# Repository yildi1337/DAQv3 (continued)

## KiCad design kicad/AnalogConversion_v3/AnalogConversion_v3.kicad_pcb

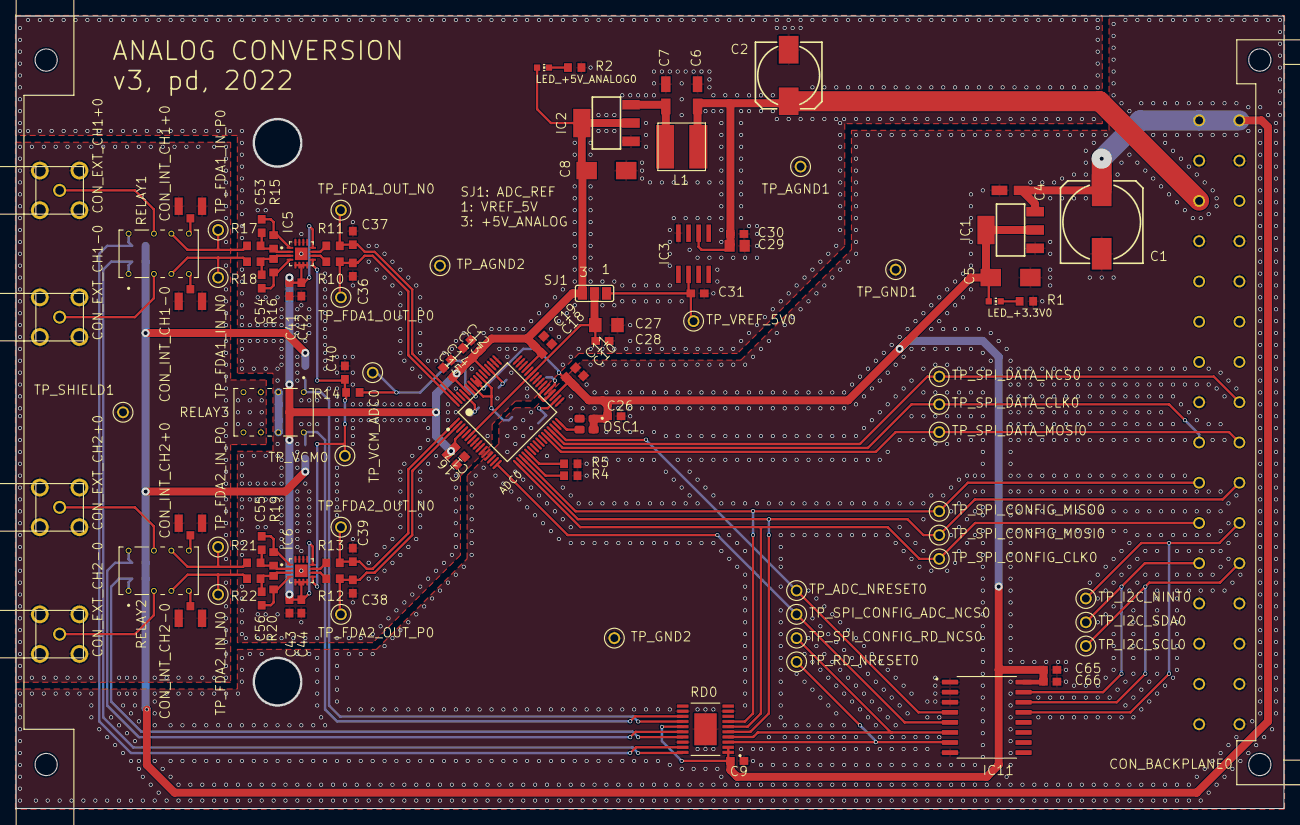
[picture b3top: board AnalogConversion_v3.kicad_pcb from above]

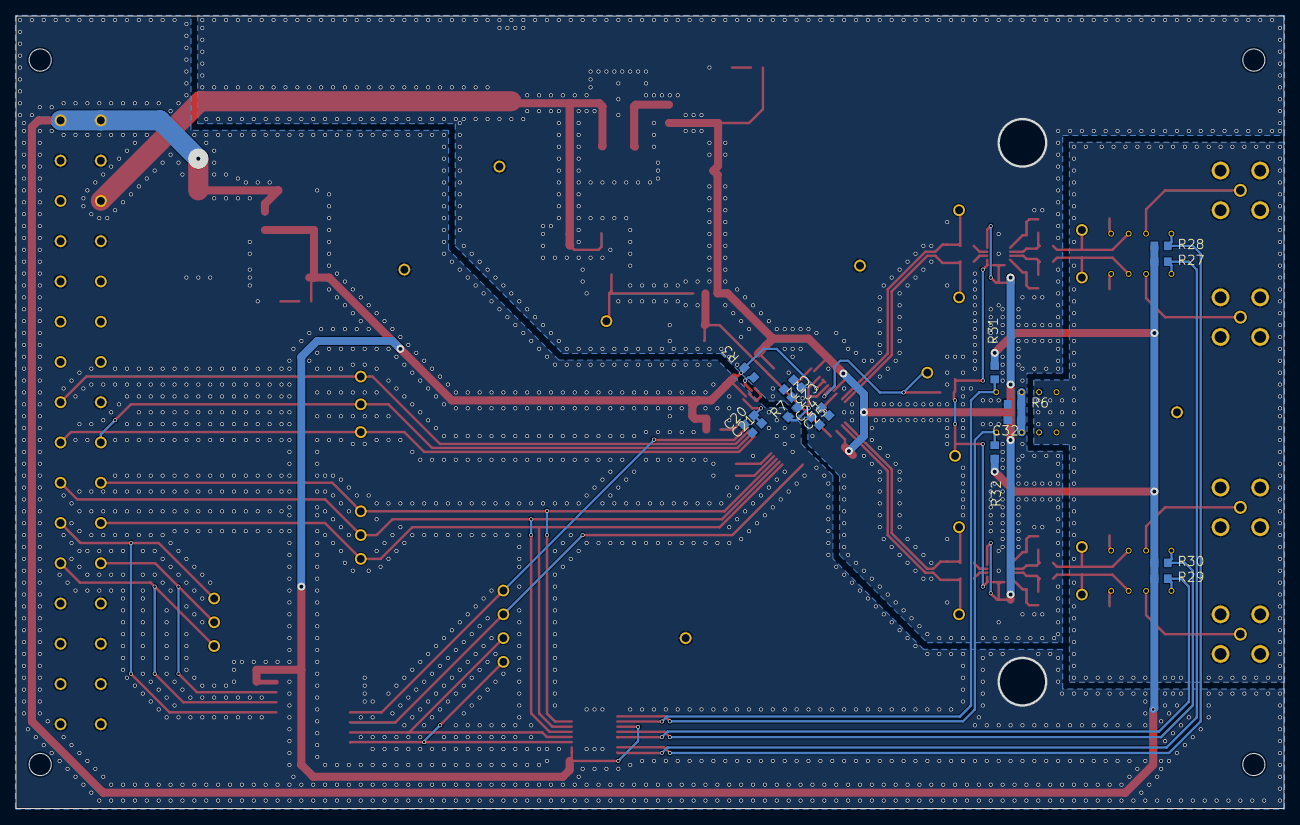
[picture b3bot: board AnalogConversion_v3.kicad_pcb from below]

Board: 2 copper layers, 160.0 x 100.0 mm, 127 parts (16 on the bottom side), 70 nets.

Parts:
ADC0: AD7768-4BSTZ; AD7768-4BSTZ_23633307
C1: 1000u/16V; 153CLV-1010_18640681
C2: 100u/25V; 153CLV-0810_18640681
C4, C6, C7: 10u; CT3216_23469469
C5, C8: 22u; CT6032_23469469
C9, C10, C12, C14, C16, C18, C20, C22, C24, C26, C28, C30, C31, C40, C42, C44, C66: 100n; C0603_23469469
C11, C13, C15, C17, C19, C23, C25, C41, C43, C65: 1u; C0603_23469469
C21: 10u; C0603_23469469
C27: 22u; C1206_23469469
C29: 10u/16V; C0805_23469469
C32: 10n; C0603_23469469
C36, C37, C38, C39: 82p; C0603_23469469
C53, C54, C55, C56: 220p; C0603_23469469
CON_BACKPLANE0: 09031326921; 09031326921_33573412
CON_EXT_CH1+0, CON_EXT_CH1-0, CON_EXT_CH2+0, CON_EXT_CH2-0: DELOCK_65848; DELOCK_65848_34726205
CON_INT_CH1+0, CON_INT_CH1-0, CON_INT_CH2+0, CON_INT_CH2-0: 2337019-1; 2337019-1_28281051
IC1: LM1117IMP-3.3; SOT223_23469477
IC2: LM1117MP-5.0; SOT223_23469477
IC3: ADR445ARZ; ADR445ARZ_35478497
IC5, IC6: ADA4945-1ACPZ-R7; ADA4945-1ACPZ-R7_22669072
IC11: TCA9534ADWR; TCA9534ADWR_34728514
L1: 100u; VLS6045AF-101M_31421361
LED_+3.3V0, LED_+5V_ANALOG0: CHIP-LED0603_259
OSC1: SG-210STF 32.7680ML3; SG-210STF-32.7680ML3_23634516
PCB_BRACKET0: 60807-011; 60807-011_33573280
R1: 750; R0603_23469469
R2: 1.8k; R0603_23469469
R3: 10k; R0603_23469469
R4, R5: 1k; R0603_23469469
R6: 1M; R0603_23469469
R7: 0; R0603_23469469
R10, R11, R12, R13: 82; R0603_23469469
R14: 47; R0603_23469469
R15, R16, R17, R18, R19, R20, R21, R22: 470; R0603_23469469
R27, R28, R29, R30, R31, R32: 100; R0603_23469469
RD0: MAX4820EUP+; MAX4820EUP+_31436371
RELAY1, RELAY2, RELAY3: 5-1462037-8; 5-1462037-8_31429267
SJ1: SJ_2_23508320
TP_ADC_NRESET0: RSPRO-1MM-TERMINAL-POST-2622034_23908750
TP_AGND1, TP_AGND2: RSPRO-1MM-TERMINAL-POST-2622034_23908750
TP_FDA1_IN_N0, TP_FDA1_IN_P0, TP_FDA1_OUT_N0, TP_FDA1_OUT_P0, TP_FDA2_IN_N0, TP_FDA2_IN_P0, TP_FDA2_OUT_N0, TP_FDA2_OUT_P0: RSPRO-1MM-TERMINAL-POST-2622034_23908750
TP_GND1, TP_GND2: RSPRO-1MM-TERMINAL-POST-2622034_23908750
TP_I2C_NINT0, TP_I2C_SCL0, TP_I2C_SDA0: RSPRO-1MM-TERMINAL-POST-2622034_23908750
TP_RD_NRESET0: RSPRO-1MM-TERMINAL-POST-2622034_23908750
TP_SHIELD1: RSPRO-1MM-TERMINAL-POST-2622034_23908750
TP_SPI_CONFIG_ADC_NCS0: RSPRO-1MM-TERMINAL-POST-2622034_23908750
TP_SPI_CONFIG_CLK0: RSPRO-1MM-TERMINAL-POST-2622034_23908750
TP_SPI_CONFIG_MISO0: RSPRO-1MM-TERMINAL-POST-2622034_23908750
TP_SPI_CONFIG_MOSI0: RSPRO-1MM-TERMINAL-POST-2622034_23908750
TP_SPI_CONFIG_RD_NCS0: RSPRO-1MM-TERMINAL-POST-2622034_23908750
TP_SPI_DATA_CLK0: RSPRO-1MM-TERMINAL-POST-2622034_23908750
TP_SPI_DATA_MOSI0: RSPRO-1MM-TERMINAL-POST-2622034_23908750
TP_SPI_DATA_NCS0: RSPRO-1MM-TERMINAL-POST-2622034_23908750
TP_VCM0: RSPRO-1MM-TERMINAL-POST-2622034_23908750
TP_VCM_ADC0: RSPRO-1MM-TERMINAL-POST-2622034_23908750
TP_VREF_5V0: RSPRO-1MM-TERMINAL-POST-2622034_23908750

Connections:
+3V3: ADC0.35, ADC0.56, ADC0.57, C5.+, C9.1, C10.1, C11.1, C26.2, C65.1, C66.1, IC1.2, IC1.TAB, IC11.16, LED_+3.3V0.A, OSC1.1, OSC1.4, R3.1, RD0.1, RD0.2, RD0.15
+5V: C1.+, C4.+, CON_BACKPLANE0.1, CON_BACKPLANE0.2, IC1.3, R27.2, R28.2, R29.2, R30.2, R31.2, R32.2
+5V_ANALOG: ADC0.4, ADC0.45, ADC0.53, ADC0.60, C8.+, C12.1, C13.1, C14.1, C15.1, C16.1, C17.1, C18.1, C19.1, C41.2, C42.2, C43.2, C44.2, IC2.2, IC2.TAB, IC5.5, IC5.6, IC5.7, IC5.8, IC5.12, IC6.5, IC6.6, IC6.7, IC6.8, IC6.12, LED_+5V_ANALOG0.A, SJ1.3
+12V: C2.+, C6.+, C29.2, C30.2, CON_BACKPLANE0.5, IC3.2, L1.1
ADC_AIN0_N: ADC0.63, C37.2, R11.1, TP_FDA1_OUT_N0.P$1
ADC_AIN0_P: ADC0.64, C36.1, R10.1, TP_FDA1_OUT_P0.P$1
ADC_AIN1_N: ADC0.1, C39.2, R13.1, TP_FDA2_OUT_N0.P$1
ADC_AIN1_P: ADC0.2, C38.1, R12.1, TP_FDA2_OUT_P0.P$1
ADC_MCLK: ADC0.32, OSC1.3
ADC_NRESET: ADC0.30, IC11.4, TP_ADC_NRESET0.P$1
ADC_REF: ADC0.6, ADC0.43, C27.1, C28.1, SJ1.2
AGND: ADC0.3, ADC0.5, ADC0.7, ADC0.8, ADC0.9, ADC0.10, ADC0.39, ADC0.40, ADC0.41, ADC0.42, ADC0.44, ADC0.46, ADC0.47, ADC0.48, ADC0.49, ADC0.50, ADC0.51, ADC0.54, ADC0.62, C2.-, C6.-, C7.-, C8.-, C12.2, C13.2, C14.2, C15.2, C16.2, C17.2, C18.2, C19.2, C22.2, C23.2, C24.2, C25.2, C27.2, C28.2, C29.1, C30.1, C31.1, C32.2, C36.2, C37.1, C38.2, C39.1, C40.2, C41.1, C42.1, C43.1, C44.1, IC2.1, IC3.4, IC5.13, IC5.14, IC5.15, IC5.16, IC5.17, IC6.13, IC6.14, IC6.15, IC6.16, IC6.17, R2.2, R6.2, R7.1, TP_AGND1.P$1, TP_AGND2.P$1
CON_EXT_CH1+: CON_EXT_CH1+0.S, RELAY1.7
CON_EXT_CH1-: CON_EXT_CH1-0.S, RELAY1.2
CON_EXT_CH2+: CON_EXT_CH2+0.S, RELAY2.7
CON_EXT_CH2-: CON_EXT_CH2-0.S, RELAY2.2
CON_INT_CH1+: CON_INT_CH1+0.S, RELAY1.5
CON_INT_CH1-: CON_INT_CH1-0.S, RELAY1.4
CON_INT_CH2+: CON_INT_CH2+0.S, RELAY2.5
CON_INT_CH2-: CON_INT_CH2-0.S, RELAY2.4
DIN: ADC0.21, R5.2
DNC/DGND: ADC0.20, R4.2
DREGCAP: ADC0.34, C20.1, C21.1
FDA1_IN_N: R18.2, RELAY1.3, TP_FDA1_IN_N0.P$1
FDA1_IN_P: R17.2, RELAY1.6, TP_FDA1_IN_P0.P$1
FDA2_IN_N: R22.2, RELAY2.3, TP_FDA2_IN_N0.P$1
FDA2_IN_P: R21.2, RELAY2.6, TP_FDA2_IN_P0.P$1
GND: ADC0.31, ADC0.33, ADC0.55, ADC0.58, C1.-, C4.-, C5.-, C9.2, C10.2, C11.2, C20.2, C21.2, C26.1, C65.2, C66.2, CON_BACKPLANE0.3, CON_BACKPLANE0.4, CON_BACKPLANE0.7, CON_BACKPLANE0.8, CON_BACKPLANE0.10, CON_BACKPLANE0.15, CON_BACKPLANE0.25, CON_BACKPLANE0.26, CON_BACKPLANE0.27, CON_BACKPLANE0.28, CON_BACKPLANE0.29, CON_BACKPLANE0.30, CON_BACKPLANE0.31, CON_BACKPLANE0.32, IC1.1, IC11.1, IC11.2, IC11.3, IC11.8, OSC1.2, R1.2, R4.1, R5.1, R7.2, RD0.9, RD0.12, RD0.18, RD0.21, TP_GND1.P$1, TP_GND2.P$1
I2C_NINT: CON_BACKPLANE0.22, IC11.13, TP_I2C_NINT0.P$1
I2C_SCL: CON_BACKPLANE0.24, IC11.14, TP_I2C_SCL0.P$1
I2C_SDA: CON_BACKPLANE0.23, IC11.15, TP_I2C_SDA0.P$1
unnamed: C32.1, R6.1, RELAY3.2, RELAY3.7
unnamed: C7.+, IC2.3, L1.2
unnamed: IC6.10, R12.2
unnamed: IC5.10, R10.2
unnamed: IC5.11, R11.2
unnamed: IC6.11, R13.2
unnamed: C53.1, IC5.2, R15.2, R17.1
unnamed: C53.2, IC5.1, R15.1
unnamed: C54.1, IC5.4, R16.1
unnamed: C54.2, IC5.3, R16.2, R18.1
unnamed: C55.1, IC6.2, R19.2, R21.1
unnamed: C55.2, IC6.1, R19.1
unnamed: C56.2, IC6.3, R20.2, R22.1
unnamed: C56.1, IC6.4, R20.1
unnamed: LED_+3.3V0.C, R1.1
unnamed: LED_+5V_ANALOG0.C, R2.1
unnamed: ADC0.36, ADC0.38
unnamed: ADC0.37, R3.2
RD_NRESET: IC11.7, RD0.3, TP_RD_NRESET0.P$1
RD_OUT1: R27.1, RD0.20, RELAY1.1
RD_OUT2: R28.1, RD0.19, RELAY1.8
RD_OUT3: R29.1, RD0.17, RELAY2.1
RD_OUT4: R30.1, RD0.16, RELAY2.8
RD_OUT5: R31.1, RD0.14, RELAY3.1
RD_OUT6: R32.1, RD0.13, RELAY3.8
REGCAPA: ADC0.61, C24.1, C25.1
REGCAPB: ADC0.52, C22.1, C23.1
SHIELD: CON_EXT_CH1+0.G1, CON_EXT_CH1+0.G2, CON_EXT_CH1+0.G3, CON_EXT_CH1+0.G4, CON_EXT_CH1-0.G1, CON_EXT_CH1-0.G2, CON_EXT_CH1-0.G3, CON_EXT_CH1-0.G4, CON_EXT_CH2+0.G1, CON_EXT_CH2+0.G2, CON_EXT_CH2+0.G3, CON_EXT_CH2+0.G4, CON_EXT_CH2-0.G1, CON_EXT_CH2-0.G2, CON_EXT_CH2-0.G3, CON_EXT_CH2-0.G4, CON_INT_CH1+0.G1, CON_INT_CH1+0.G2, CON_INT_CH1-0.G1, CON_INT_CH1-0.G2, CON_INT_CH2+0.G1, CON_INT_CH2+0.G2, CON_INT_CH2-0.G1, CON_INT_CH2-0.G2, RELAY3.3, RELAY3.6, TP_SHIELD1.P$1
SPI_CONFIG_ADC_NCS: ADC0.16, IC11.5, TP_SPI_CONFIG_ADC_NCS0.P$1
SPI_CONFIG_CLK: ADC0.17, CON_BACKPLANE0.21, RD0.6, TP_SPI_CONFIG_CLK0.P$1
SPI_CONFIG_MISO: ADC0.19, CON_BACKPLANE0.19, RD0.7, TP_SPI_CONFIG_MISO0.P$1
SPI_CONFIG_MOSI: ADC0.18, CON_BACKPLANE0.20, RD0.5, TP_SPI_CONFIG_MOSI0.P$1
SPI_CONFIG_RD_NCS: IC11.6, RD0.4, TP_SPI_CONFIG_RD_NCS0.P$1
SPI_DATA_CLK: ADC0.28, CON_BACKPLANE0.17, TP_SPI_DATA_CLK0.P$1
SPI_DATA_MOSI: ADC0.27, CON_BACKPLANE0.18, TP_SPI_DATA_MOSI0.P$1
SPI_DATA_NCS: ADC0.29, CON_BACKPLANE0.16, TP_SPI_DATA_NCS0.P$1
VCM: C40.1, IC5.9, IC6.9, R14.2, TP_VCM0.P$1
VCM_ADC: ADC0.59, R14.1, TP_VCM_ADC0.P$1
VREF_5V: C31.2, IC3.6, SJ1.1, TP_VREF_5V0.P$1

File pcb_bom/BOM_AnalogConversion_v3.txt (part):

Qty Value                Device                          Package                         Parts                                                                                                                                                                                                                                                                                                                                                                                                                              Description                          POPULARITY SPICEPREFIX
2                        LEDCHIP-LED0603                 CHIP-LED0603                    LED_+3.3V, LED_+5V_ANALOG                                                                                                                                                                                                                                                                                                                                                                                                          LED                                  26                    
29                       RSPRO-1MM-TERMINAL-POST-2622034 RSPRO-1MM-TERMINAL-POST-2622034 TP_ADC_NRESET, TP_AGND1, TP_AGND2, TP_FDA1_IN_N, TP_FDA1_IN_P, TP_FDA1_OUT_N, TP_FDA1_OUT_P, TP_FDA2_IN_N, TP_FDA2_IN_P, TP_FDA2_OUT_N, TP_FDA2_OUT_P, TP_GND1, TP_GND2, TP_I2C_NINT, TP_I2C_SCL, TP_I2C_SDA, TP_RD_NRESET, TP_SHIELD1, TP_SPI_CONFIG_ADC_NCS, TP_SPI_CONFIG_CLK, TP_SPI_CONFIG_MISO, TP_SPI_CONFIG_MOSI, TP_SPI_CONFIG_RD_NCS, TP_SPI_DATA_CLK, TP_SPI_DATA_MOSI, TP_SPI_DATA_NCS, TP_VCM, TP_VCM_ADC, TP_VREF_5V                                                            
1                        SJ2W                            SJ_2                            SJ1                                                                                                                                                                                                                                                                                                                                                                                                                                SMD solder JUMPER                    7                     
1   0                    R-EU_R0603                      R0603                           R7                                                                                                                                                                                                                                                                                                                                                                                                                                 RESISTOR, European symbol            70         R          
1   09031326921          09031326921                     09031326921                     CON_BACKPLANE                                                                                                                                                                                                                                                                                                                                                                                                                                                                                 
1   1.8k                 R-EU_R0603                      R0603                           R2                                                                                                                                                                                                                                                                                                                                                                                                                                 RESISTOR, European symbol            70         R          
6   100                  R-EU_R0603                      R0603                           R27, R28, R29, R30, R31, R32                                                                                                                                                                                                                                                                                                                                                                                                       RESISTOR, European symbol            70         R          
1   1000u/16V            CPOL-EU153CLV-1010              153CLV-1010                     C1                                                                                                                                                                                                                                                                                                                                                                                                                                 POLARIZED CAPACITOR, European symbol 0          C          
17  100n                 C-EUC0603                       C0603                           C9, C10, C12, C14, C16, C18, C20, C22, C24, C26, C28, C30, C31, C40, C42, C44, C66                                                                                                                                                                                                                                                                                                                                                 CAPACITOR, European symbol           73         C          
1   100u                 VLS6045AF-101M                  VLS6045AF-101M                  L1                                                                                                                                                                                                                                                                                                                                                                                                                                                                                            
1   100u/25V             CPOL-EU153CLV-0810              153CLV-0810                     C2                                                                                                                                                                                                                                                                                                                                                                                                                                 POLARIZED CAPACITOR, European symbol 4          C          
1   10k                  R-EU_R0603                      R0603                           R3                                                                                                                                                                                                                                                                                                                                                                                                                                 RESISTOR, European symbol            70         R          
1   10n                  C-EUC0603                       C0603                           C32                                                                                                                                                                                                                                                                                                                                                                                                                                CAPACITOR, European symbol           73         C          
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
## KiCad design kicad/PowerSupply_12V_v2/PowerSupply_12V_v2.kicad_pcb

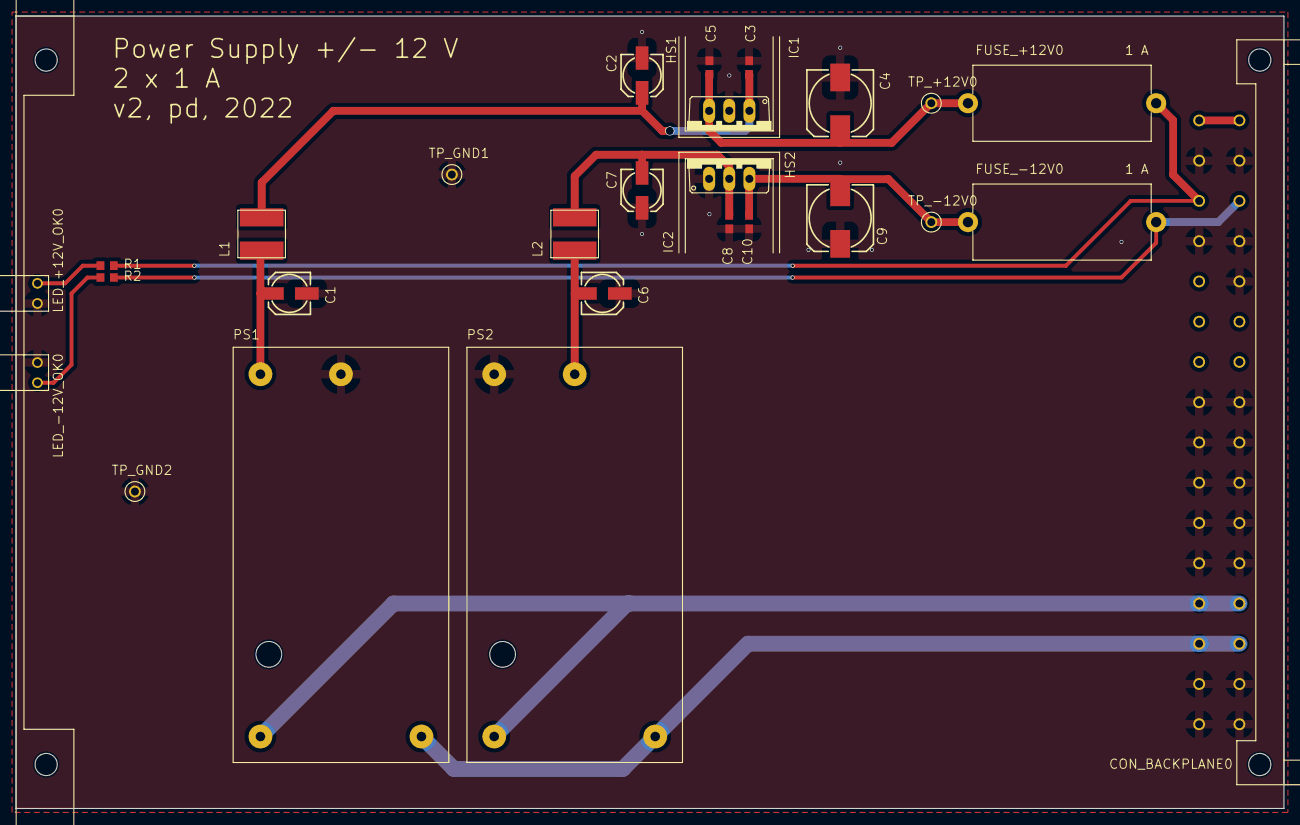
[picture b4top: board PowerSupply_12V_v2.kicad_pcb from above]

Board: 2 copper layers, 160.0 x 100.0 mm, 30 parts (0 on the bottom side), 14 nets.

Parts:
C1, C2, C6, C7: 22u/25V; 153CLV-0505_18640681
C3, C5, C8, C10: 100n; C0603_18640681
C4, C9: 100u/25V; 153CLV-0810_18640681
CON_BACKPLANE0: 09031326921; 09031326921_33573412
FUSE_+12V0: 0031.8201; 0031.8201_24323731
FUSE_-12V0: 0031.8201; 0031.8201_24323731
HS1, HS2: FK 237 SA 220 O; FK_237_SA_220_O_33584193
IC1: L7812CV; L7812CV_35690097
IC2: L7912CV; L7912CV_35690127
L1, L2: VLS6045AF-101M; VLS6045AF-101M_31421361
LED_+12V_OK0: 113-314-04; 113-314-04_33630242
LED_-12V_OK0: 113-314-04; 113-314-04_33630242
PCB_BRACKET0: 60807-011; 60807-011_33573280
PS1, PS2: TMLM_20115; TMLM_201XX_35462927
R1, R2: 680; R0603_18640681
TP_+12V0: RSPRO-1MM-TERMINAL-POST-2622034_23908750
TP_-12V0: RSPRO-1MM-TERMINAL-POST-2622034_23908750
TP_GND1, TP_GND2: RSPRO-1MM-TERMINAL-POST-2622034_23908750

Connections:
+5V: CON_BACKPLANE0.1, CON_BACKPLANE0.2
+12V: CON_BACKPLANE0.5, FUSE_+12V0.2, R1.2
-12V: CON_BACKPLANE0.6, FUSE_-12V0.2, R2.1
GND: C1.-, C2.-, C3.2, C4.-, C5.2, C6.+, C7.+, C8.1, C9.+, C10.1, CON_BACKPLANE0.3, CON_BACKPLANE0.4, CON_BACKPLANE0.7, CON_BACKPLANE0.8, CON_BACKPLANE0.10, CON_BACKPLANE0.15, CON_BACKPLANE0.16, CON_BACKPLANE0.17, CON_BACKPLANE0.18, CON_BACKPLANE0.19, CON_BACKPLANE0.20, CON_BACKPLANE0.21, CON_BACKPLANE0.22, CON_BACKPLANE0.23, CON_BACKPLANE0.24, CON_BACKPLANE0.29, CON_BACKPLANE0.30, CON_BACKPLANE0.31, CON_BACKPLANE0.32, IC1.2, IC2.1, LED_+12V_OK0.-, LED_-12V_OK0.+, PS1.3, PS2.2, TP_GND1.P$1, TP_GND2.P$1
L: CON_BACKPLANE0.27, CON_BACKPLANE0.28, PS1.5, PS2.5
N: CON_BACKPLANE0.25, CON_BACKPLANE0.26, PS1.6, PS2.6
unnamed: C7.-, C8.2, IC2.2, L2.1
unnamed: LED_-12V_OK0.-, R2.2
unnamed: C9.-, C10.2, FUSE_-12V0.1, IC2.3, TP_-12V0.P$1
unnamed: C1.+, L1.1, PS1.2
unnamed: C6.-, L2.2, PS2.3
unnamed: LED_+12V_OK0.+, R1.1
unnamed: C4.+, C5.1, FUSE_+12V0.1, IC1.3, TP_+12V0.P$1
unnamed: C2.+, C3.1, IC1.1, L1.2

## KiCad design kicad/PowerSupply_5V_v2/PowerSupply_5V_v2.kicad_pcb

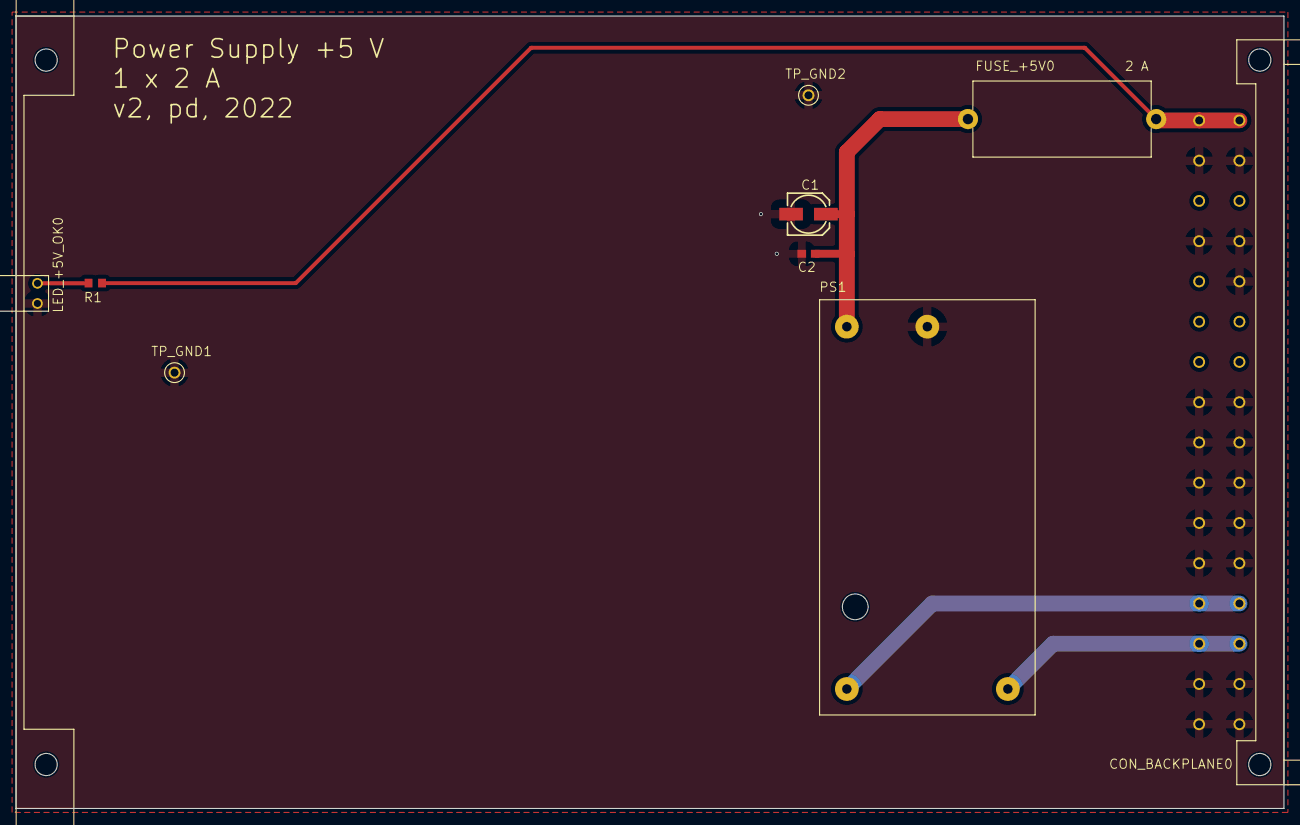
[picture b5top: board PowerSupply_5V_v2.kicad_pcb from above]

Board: 2 copper layers, 160.0 x 100.0 mm, 10 parts (0 on the bottom side), 6 nets.

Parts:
C1: 47u/16V; 153CLV-0505_18640681
C2: 100n; C0603_18640681
CON_BACKPLANE0: 09031326921; 09031326921_33573412
FUSE_+5V0: 0031.8201; 0031.8201_24323731
LED_+5V_OK0: 113-314-04; 113-314-04_33630242
PCB_BRACKET0: 60807-011; 60807-011_33573280
PS1: TMLM_20105; TMLM_201XX_35462927
R1: 150; R0603_18640681
TP_GND1, TP_GND2: RSPRO-1MM-TERMINAL-POST-2622034_23908750

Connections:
+5V: CON_BACKPLANE0.1, CON_BACKPLANE0.2, FUSE_+5V0.2, R1.2
GND: C1.-, C2.2, CON_BACKPLANE0.3, CON_BACKPLANE0.4, CON_BACKPLANE0.7, CON_BACKPLANE0.8, CON_BACKPLANE0.10, CON_BACKPLANE0.15, CON_BACKPLANE0.16, CON_BACKPLANE0.17, CON_BACKPLANE0.18, CON_BACKPLANE0.19, CON_BACKPLANE0.20, CON_BACKPLANE0.21, CON_BACKPLANE0.22, CON_BACKPLANE0.23, CON_BACKPLANE0.24, CON_BACKPLANE0.29, CON_BACKPLANE0.30, CON_BACKPLANE0.31, CON_BACKPLANE0.32, LED_+5V_OK0.-, PS1.3, TP_GND1.P$1, TP_GND2.P$1
L: CON_BACKPLANE0.27, CON_BACKPLANE0.28, PS1.5
N: CON_BACKPLANE0.25, CON_BACKPLANE0.26, PS1.6
unnamed: C1.+, C2.1, FUSE_+5V0.1, PS1.2
unnamed: LED_+5V_OK0.+, R1.1

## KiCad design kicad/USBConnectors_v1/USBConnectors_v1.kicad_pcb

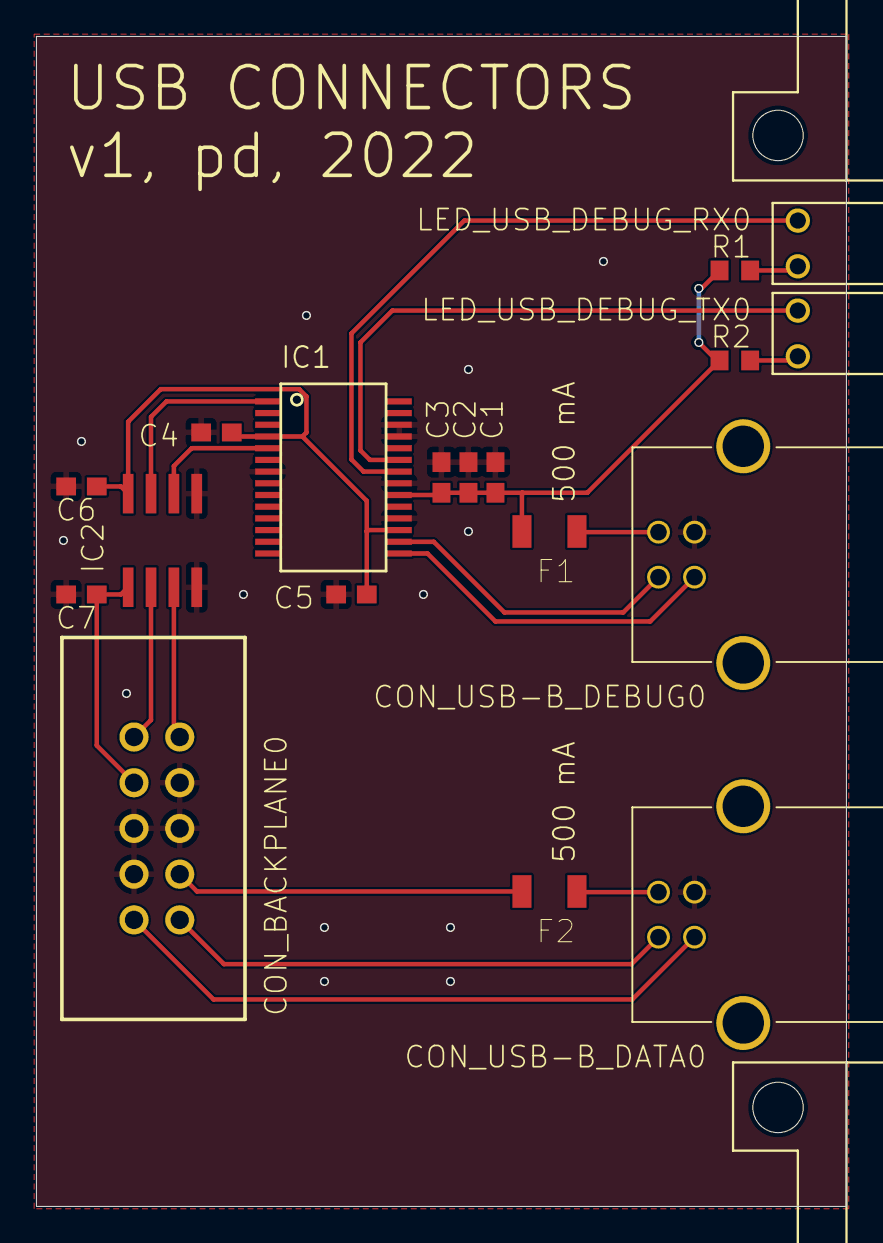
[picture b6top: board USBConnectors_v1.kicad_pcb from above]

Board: 2 copper layers, 45.0 x 65.0 mm, 20 parts (0 on the bottom side), 19 nets.

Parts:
C1: 10n; C0603_23469469
C2, C4, C5, C6, C7: 100n; C0603_23469469
C3: 4.7u; C0603_23469469
CON_BACKPLANE0: TST-105-01-T-D; TST-105-01-T-D_27603653
CON_USB-B_DATA0: 61729-1011BLF; 61729-1011BLF_23524969
CON_USB-B_DEBUG0: 61729-1011BLF; 61729-1011BLF_23524969
F1, F2: 500 mA; LITTELFUSE_466_SERIES_24171630
IC1: FT232RL; FT232RL_24048598
IC2: ADUM1201ARZ; SO8_18370689
LED_USB_DEBUG_RX0: 113-311-04; 113-311-04_33651165
LED_USB_DEBUG_TX0: 113-305-04; 113-305-04_33651180
PCB_BRACKET1: 60807-181_A; 60807-181_A_33908866
PCB_BRACKET2: 60807-181_B; 60807-181_B_33908866
R1, R2: 1.5k; R0603_23469469

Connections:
GND: C1.2, C2.1, C3.1, C4.2, C5.2, C6.2, C7.1, CON_BACKPLANE0.4, CON_BACKPLANE0.5, CON_BACKPLANE0.6, CON_BACKPLANE0.7, CON_USB-B_DATA0.4, CON_USB-B_DEBUG0.4, IC1.7, IC1.18, IC1.21, IC1.25, IC1.26, IC2.4, IC2.5
unnamed: CON_USB-B_DEBUG0.1, F1.1
unnamed: LED_USB_DEBUG_RX0.+, R1.2
unnamed: LED_USB_DEBUG_TX0.+, R2.2
unnamed: C4.1, C5.1, C6.1, IC1.4, IC1.17, IC2.8
unnamed: IC1.22, LED_USB_DEBUG_RX0.-
unnamed: IC1.23, LED_USB_DEBUG_TX0.-
USART_RX: IC1.1, IC2.7
USART_RX_ISOLATED: CON_BACKPLANE0.10, IC2.2
USART_TX: IC1.5, IC2.6
USART_TX_ISOLATED: CON_BACKPLANE0.9, IC2.3
USART_VDD: C7.2, CON_BACKPLANE0.8, IC2.1
USB-B_DATA_DM: CON_BACKPLANE0.1, CON_USB-B_DATA0.2
USB-B_DATA_DP: CON_BACKPLANE0.2, CON_USB-B_DATA0.3
USB-B_DEBUG_DM: CON_USB-B_DEBUG0.2, IC1.16
USB-B_DEBUG_DP: CON_USB-B_DEBUG0.3, IC1.15
VBUS_USB-B_DATA_FUSED: CON_BACKPLANE0.3, F2.2
VBUS_USB-B_DEBUG_FUSED: C1.1, C2.2, C3.2, F1.2, IC1.20, R1.1, R2.1
VBUS_USB-B_NF: CON_USB-B_DATA0.1, F2.1

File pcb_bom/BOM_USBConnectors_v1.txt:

Qty Value          Device                Package               Parts                           Description                POPULARITY SPICEPREFIX
2   1.5k           R-EU_R0603            R0603                 R1, R2                          RESISTOR, European symbol  70         R          
5   100n           C-EUC0603             C0603                 C2, C4, C5, C6, C7              CAPACITOR, European symbol 73         C          
1   10n            C-EUC0603             C0603                 C1                              CAPACITOR, European symbol 73         C          
1   113-305-04     113-305-04            113-305-04            LED_USB_DEBUG_TX                                                                 
1   113-311-04     113-311-04            113-311-04            LED_USB_DEBUG_RX                                                                 
1   4.7u           C-EUC0603             C0603                 C3                              CAPACITOR, European symbol 73         C          
2   500 mA         LITTELFUSE_466_SERIES LITTELFUSE_466_SERIES F1, F2                                                                           
1   60807-181_A    60807-181_A           60807-181_A           PCB_BRACKET1                                                                     
1   60807-181_B    60807-181_B           60807-181_B           PCB_BRACKET2                                                                     
2   61729-1011BLF  61729-1011BLF         61729-1011BLF         CON_USB-B_DATA, CON_USB-B_DEBUG                                                  
1   ADUM1201ARZ    ADUM1201              SO8                   IC2                                                                              
1   FT232RL        FT232RL               FT232RL               IC1                                                                              
1   TST-105-01-T-D TST-105-01-T-D        TST-105-01-T-D        CON_BACKPLANE
